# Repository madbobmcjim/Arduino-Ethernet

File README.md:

# Arduino-Ethernet
Board design to connect an Arduino Pro Mini to an Ethernet socket, with sensor ports and passive PoE.

This board is designed to be an IOT sensor node, with connections for:
* DS18b20 Temperature sensor
* Door sensor switches
* Breakout header for other boards/sensors

# First prototype boards are in!

# ToDo
* Rearrange device numbers
* Move SCL/SDA pins
* Rewire Ethernet pins - TP-Out too close to socket
* Greater distance between Eth port and VRM
* Change C15 for a Radial capacitor

# BOM 
Name|Value|Description|Link
----|-----|-----------|-----
J1|RJ45-SI52008-F|Magjack:MagJack-SI-52008-F|http://uk.farnell.com/stewart-connector/si-52008-f/modular-jack-tht-r-a-led-rj45/dp/1572195
L1|L	|Ferite Bead 0805
P1|Door1	|TE-Micro-2pin
P2|Door2	|TE-Micro-2pin
P3|Temp	|Pin_Headers:Pin_Header_Straight_1x03
P4|Alt. |Power	Pin_Headers:Pin_Header_Straight_1x02
P5|Breakout	|Pin_Headers:Pin_Header_Straight_2x06
P6|Arduino Pins 1	|Pin_Headers:Pin_Header_Straight_1x12
P7|Arduino Pins 2	|Pin_Headers:Pin_Header_Straight_1x12
P8|ArduinoPower	|Pin_Headers:Pin_Header_Straight_1x02
P9|I2C Pins	|Pin_Headers:Pin_Header_Straight_1x02
R1|4.7k	|Resistor 0805
R2|4.7k	|Resistor 0805
R3|4.7k	|Resistor 0805
R4|12k4_1%	|Resistor 0805
R5|10k	|Resistor 0805
R6|10k	|Resistor 0805
R7|10k	|Resistor 0805
R8|49.9/1%	|Resistor 0805
R9|49.9/1%	|Resistor 0805
R10|49.9/1%	|Resistor 0805
R13|49.9/1%	|Resistor 0805
R14|180	|Resistor 0805
R15|180	|Resistor 0805
R16|10k	|Resistor 0805
R17|10k	|Resistor 0805
R18|10k	|Resistor 0805
R19|10k	|Resistor 0805
R20|10k	|Resistor 0805
R21|10k	|Resistor 0805
R22|10k	|Resistor 0805
R23|10k	|Resistor 0805
R24|10k	|Resistor 0805
R25|1M	|Resistor 0805
R26|10k	|Resistor 0805
R27|10k	|Resistor 0805
R28|10k	|Resistor 0805
R29|10R/1%	|Resistor 0805
C1|100nF	|Capacitor 0805
C2|100nF	|Capacitor 0805
C3|100nF	|Capacitor 0805
C4|100nF	|Capacitor 0805
C5|4u7	|Capacitor 0805
C6|10pF	|Capacitor 0805
C7|10pF	|Capacitor 0805
C8|10n	|Capacitor 0805
C9|10nF	|Capacitor 0805
C10|100nF	|Capacitor 0805
C11|100nF	|Capacitor 0805
C12|10uF	|Capacitor 0805
C13|10uF	|Capacitor 0805
C14|100nF	|Capacitor 0805
C15|22uF	|Capacitor 0805
C16|100nF	|Capacitor 0805
C17|100nF	|Capacitor 0805
C18|6.8nF	|Capacitor 0805
C19|6.8nF	|Capacitor 0805
U1|SPX2920U-3.3	|TO_SOT_Packages_THT:TO-220_Neutral123_Vertical
U2|W5500	|Housings_QFP:LQFP-48_7x7mm_Pitch0.5mm
Y1|25Mhz	|Crystals:Crystal_HC49-SD_SMD

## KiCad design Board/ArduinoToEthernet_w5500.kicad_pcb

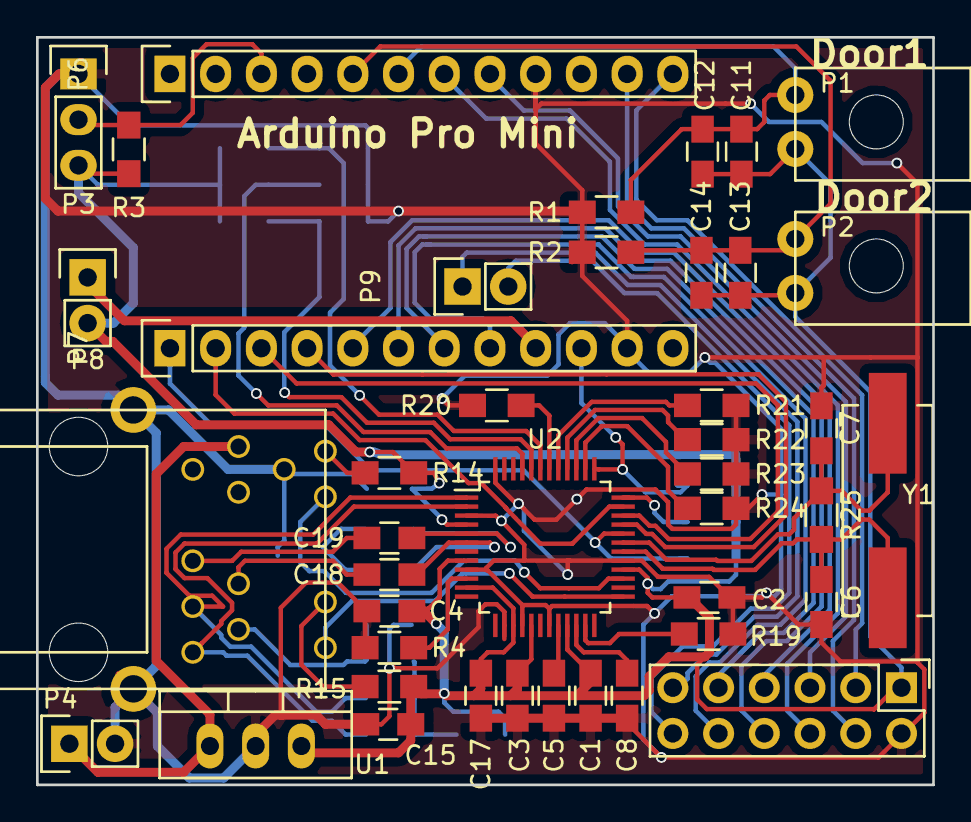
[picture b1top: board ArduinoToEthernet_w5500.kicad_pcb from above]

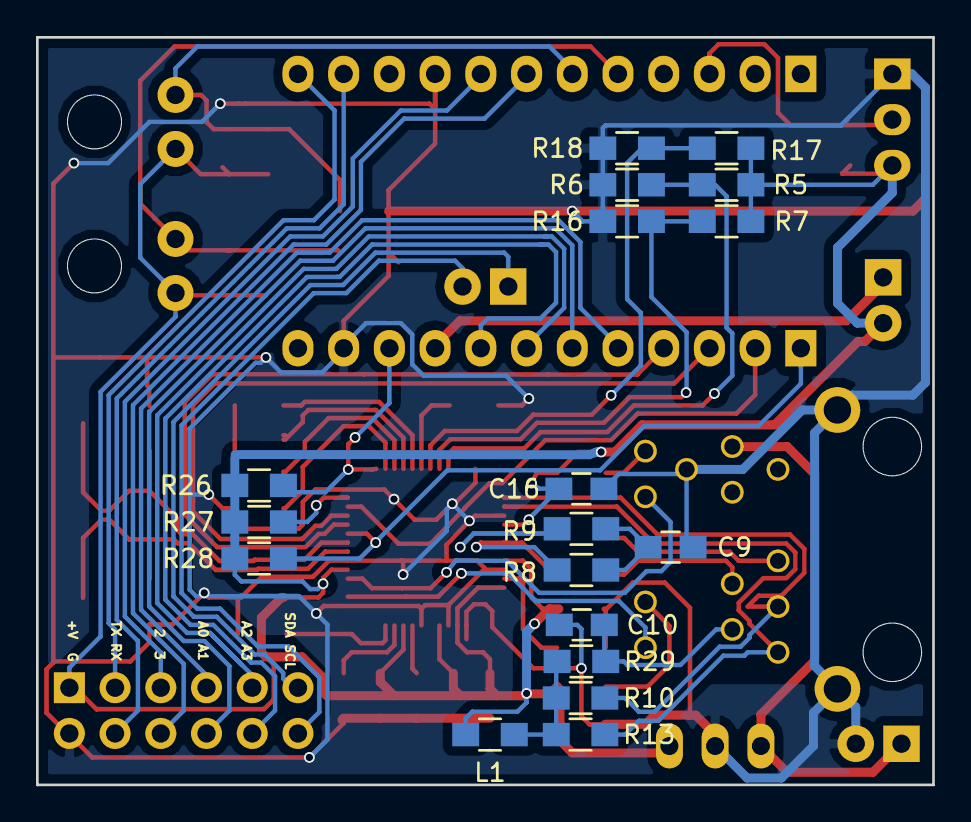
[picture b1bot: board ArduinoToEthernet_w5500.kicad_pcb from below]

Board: 2 copper layers, 49.8 x 41.5 mm, 60 parts (18 on the bottom side), 50 nets.

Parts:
C1, C2, C3, C4, C10, C11, C14, C16, C17: 100nF; C_0805_HandSoldering
C5: 4u7; C_0805_HandSoldering
C6, C7: 10pF; C_0805_HandSoldering
C8: 10n; C_0805_HandSoldering
C9: 10nF; C_0805_HandSoldering
C12, C13: 10uF; C_0805_HandSoldering
C15: 22uF; C_0805_HandSoldering
C18, C19: 6.8nF; C_0805_HandSoldering
J1: RJ45-SI52008-F; MagJack-SI-52008-F
L1: L; R_0805_HandSoldering
P1: Door1; TE-Micro-2pin
P2: Door2; TE-Micro-2pin
P3: Temp; Pin_Header_Straight_1x03
P4: CONN_01X02; Pin_Header_Straight_1x02
P5: CONN_02X06; Pin_Header_Straight_2x06
P6: TOP; Pin_Header_Straight_1x12
P7: Bottom; Pin_Header_Straight_1x12
P8: ArduinoPower; Pin_Header_Straight_1x02
P9: I2C Pins; Pin_Header_Straight_1x02
R1, R2, R3: 4.7k; R_0805_HandSoldering
R4: 12k4_1%; R_0805_HandSoldering
R5, R6, R7, R16, R17, R18, R19, R20, R21, R22, R23, R24, R26, R27, R28: 10k; R_0805_HandSoldering
R8, R9, R10, R13: 49.9/1%; R_0805_HandSoldering
R14, R15: 180; R_0805_HandSoldering
R25: 1M; R_0805_HandSoldering
R29: 10R/1%; R_0805_HandSoldering
U1: SPX2920U-3.3; TO-220_Neutral123_Vertical
U2: W5500; LQFP-48_7x7mm_Pitch0.5mm
Y1: 25Mhz; Crystal_HC49-SD_SMD

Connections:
/+3.3v: C1.1, C2.1, C3.1, C4.1, C11.1, C12.1, C13.1, C14.1, C15.1, C16.1, C17.1, L1.2, P1.2, P2.2, P3.3, P5.1, P8.2, R3.2, R5.1, R7.1, R14.1, R15.1, R17.1, R26.1, R27.1, R28.1, U1.3, U2.4, U2.8, U2.11, U2.15, U2.17, U2.21, U2.28
/GND: C1.2, C2.2, C3.2, C4.2, C5.2, C6.2, C7.2, C8.1, C9.1, C10.2, C15.2, C16.2, C17.2, J1.11, J1.13, P3.1, P4.2, P5.2, P6.9, P7.11, R1.2, R2.2, R4.2, R6.2, R16.2, R18.2, R19.2, R20.1, R21.1, R22.1, R23.1, R24.1, U1.2, U2.3, U2.9, U2.14, U2.16, U2.19, U2.29, U2.48
/INT: R27.2, U2.36
/LEDA: J1.GK, U2.27
/LEDB: J1.YK, U2.25
/MISO: P7.3, U2.34
/MOSI: P7.2, U2.35
/P2: P5.5, P6.8
/P3: P5.6, P6.7
/PA0: P5.7, P7.5
/PA1: P5.8, P7.6
/PA2: P5.9, P7.7
/PA3: P5.10, P7.8
/RD+: C18.1, J1.4
/RD-: C19.1, J1.5
/RST: P7.10, R26.2, U2.37
/RX: P5.4, P6.11
/SCK: P7.4, U2.33
/SCL: P5.11, P9.1
/SCSn: P7.1, R28.2, U2.32
/SDA: P5.12, P9.2
/SW1: C11.2, C12.2, P1.1, P6.6, R1.1
/SW2: C13.2, C14.2, P2.1, P6.5, R2.1
/TEMP: P3.2, P6.3, R3.1
/TPIN+: C18.2, R8.1, U2.6
/TPIN-: C19.2, R9.1, U2.5
/TPOUT+: J1.1, R13.2, U2.2
/TPOUT-: J1.3, R10.2, U2.1
/TX: P5.3, P6.12
/VIN: J1.10, P4.1, U1.1
/X+: C7.1, R25.1, U2.31, Y1.2
/X-: C6.1, R25.2, U2.30, Y1.1
unnamed: C5.1, U2.20
unnamed: C8.2, U2.22
unnamed: C9.2, R8.2, R9.2
unnamed: C10.1, J1.2, R29.1
unnamed: J1.GA, R14.2
unnamed: J1.YA, R15.2
unnamed: L1.1, R10.1, R13.1, R29.2
unnamed: P7.9, P8.1
unnamed: R4.1, U2.10
unnamed: R5.2, R6.1, U2.45
unnamed: R7.2, R16.1, U2.44
unnamed: R17.2, R18.1, U2.43
unnamed: R19.1, U2.23
unnamed: R20.2, U2.42
unnamed: R21.2, U2.41
unnamed: R22.2, U2.40
unnamed: R23.2, U2.39
unnamed: R24.2, U2.38

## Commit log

2017-10-16 Rename ArduinoToEthernet_w5500-cache.lib to Board/ArduinoToEthernet_w5500-cache.lib
2017-10-16 Rename ArduinoToEthernet_w5500-rescue.lib to Board/ArduinoToEthernet_w5500-rescue.lib
2017-10-16 Rename ArduinoToEthernet_w5500.bak to Board/ArduinoToEthernet_w5500.bak
2017-10-16 Rename ArduinoToEthernet_w5500.kicad_pcb to Board/ArduinoToEthernet_w5500.kicad_pcb
2017-10-16 Rename ArduinoToEthernet_w5500.kicad_pcb-bak to Board/ArduinoToEthernet_w5500.kicad_pcb-bak
2017-10-16 Rename ArduinoToEthernet_w5500.net to Board/ArduinoToEthernet_w5500.net
2017-10-16 Rename ArduinoToEthernet_w5500.pro to Board/ArduinoToEthernet_w5500.pro
2017-10-16 Rename ArduinoToEthernet_w5500.sch to Board/ArduinoToEthernet_w5500.sch
2017-10-16 Rename ArduinoToEthernet_w5500.xml to Board/ArduinoToEthernet_w5500.xml
